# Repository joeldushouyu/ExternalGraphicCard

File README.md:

# ExternalGraphicCard

This Github repo contain the documentation for the USB-To-HDMI adapter(External Graphic Card) that I designed for my Senior Project.

The __USB To HDMI Adapter__(External Graphic Card) is an attempt to reproduce device that is similar to Startech's [USB32HD4k](https://www.startech.com/en-us/display-video-adapters/usb32hd4k) device that works on Linux, Ubuntu specifically. 

Currently, the device support video streaming up to 1080p at 30HZ. 

The device is compatible to most linux distribution that support by [evdi](https://github.com/DisplayLink/evdi). Currently, the device is tested and verified on Ubuntu 20.04.

When plugging the USb 3.0 Device into the host laptop and launch the C++ program, a new display monitor will be registered in OS and image data will stream out from the USb 3.0 port to the FPGA and output in HDMI signal.

**For more info**, please refer to the [user manual](Usermanual.md), [Technical Manual](TechnicalMaunaul.md), and the [Fabrication Plan Manual](./FabricationMaunal.md)

# Demonstration

## Video & Sound in Sync
[Video link](https://github.com/joeldushouyu/ExternalGraphicCard/blob/main/videoDirectory/video-sync.mp4)

## Drag window across monitors
[Video link](https://github.com/joeldushouyu/ExternalGraphicCard/blob/main/videoDirectory/drag-window-between-monitors.mp4)

## Browing  website
[Video link](https://github.com/joeldushouyu/ExternalGraphicCard/blob/main/videoDirectory/browsing-website.mp4)

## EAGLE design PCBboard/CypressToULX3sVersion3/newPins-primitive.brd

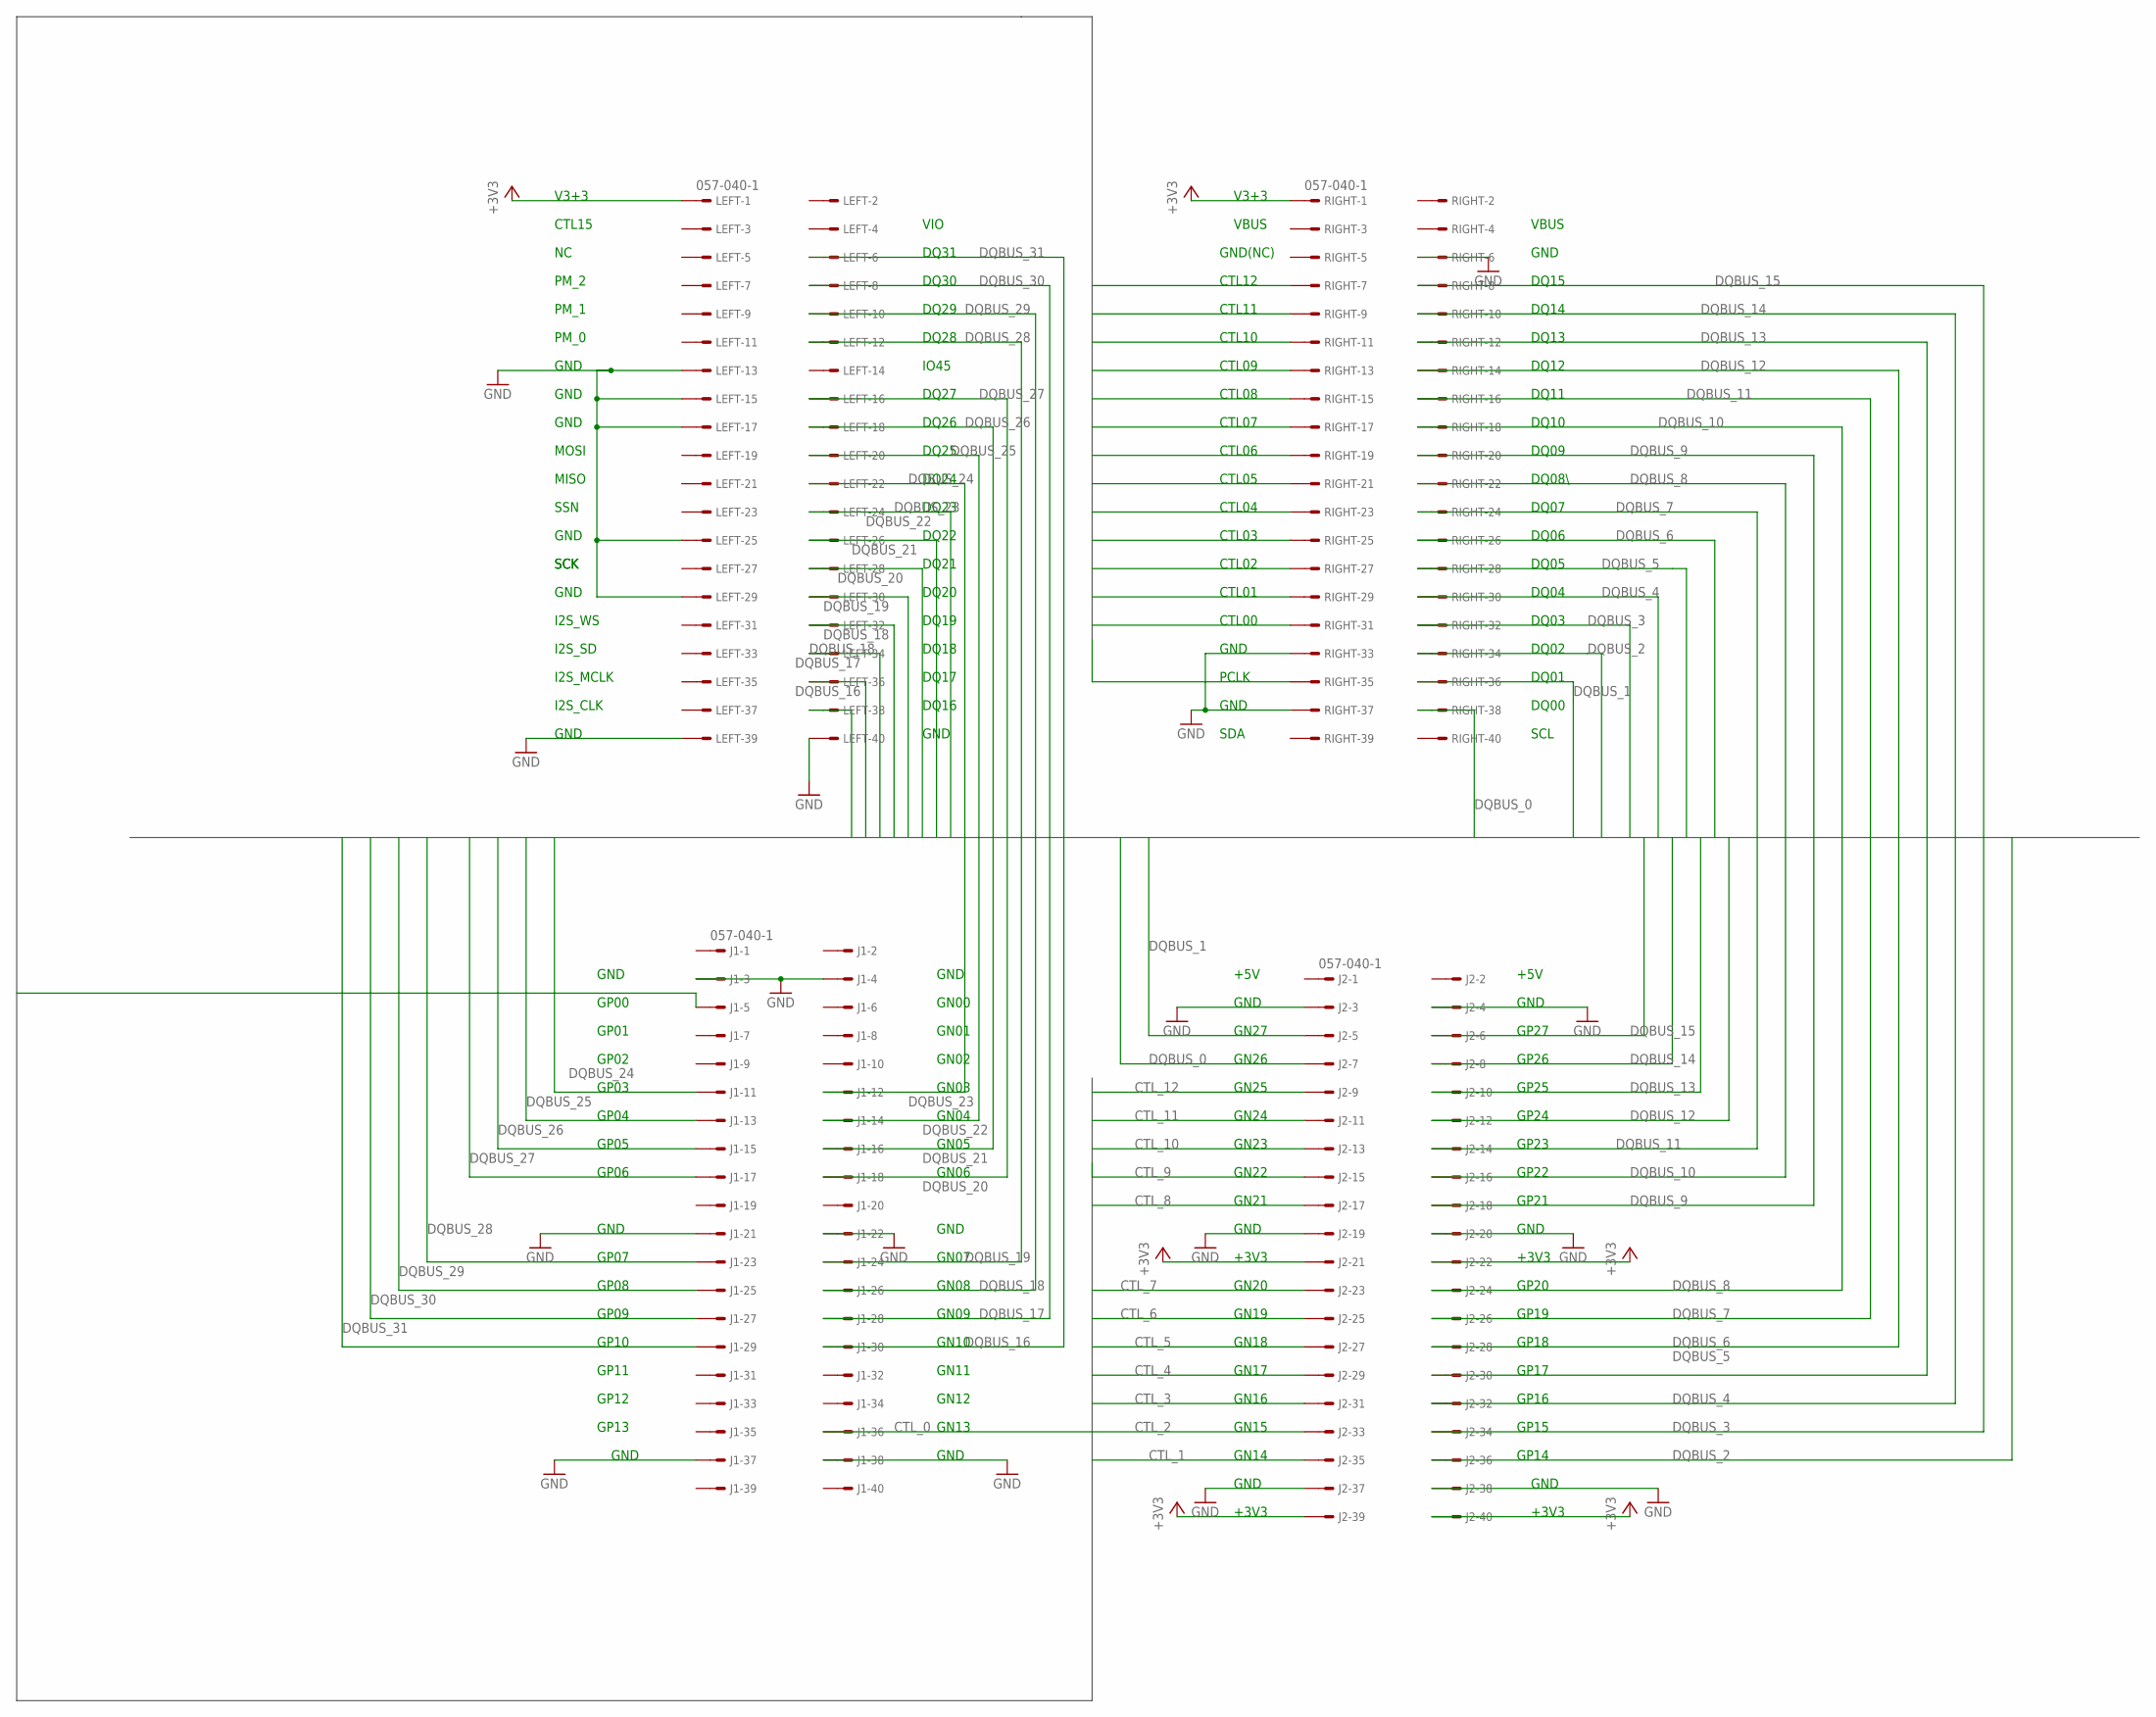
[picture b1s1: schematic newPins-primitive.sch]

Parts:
J1, J2: 057-040-1
LEFT: 057-040-1
RIGHT: 057-040-1

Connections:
+3V3: J2.21, J2.22, J2.39, J2.40, LEFT.1, RIGHT.1
CTL_0: J1.36, RIGHT.31
CTL_1: J2.35, RIGHT.29
CTL_2: J2.33, RIGHT.27
CTL_3: J2.31, RIGHT.25
CTL_4: J2.29, RIGHT.23
CTL_5: J2.27, RIGHT.21
CTL_6: J2.25, RIGHT.19
CTL_7: J2.23, RIGHT.17
CTL_8: J2.17, RIGHT.15
CTL_9: J2.15, RIGHT.13
CTL_10: J2.13, RIGHT.11
CTL_11: J2.11, RIGHT.9
CTL_12: J2.9, RIGHT.7
CTL_PCLK: J1.5, RIGHT.35
DQBUS_0: J2.7, RIGHT.38
DQBUS_1: J2.5, RIGHT.36
DQBUS_2: J2.36, RIGHT.34
DQBUS_3: J2.34, RIGHT.32
DQBUS_4: J2.32, RIGHT.30
DQBUS_5: J2.30, RIGHT.28
DQBUS_6: J2.28, RIGHT.26
DQBUS_7: J2.26, RIGHT.24
DQBUS_8: J2.24, RIGHT.22
DQBUS_9: J2.18, RIGHT.20
DQBUS_10: J2.16, RIGHT.18
DQBUS_11: J2.14, RIGHT.16
DQBUS_12: J2.12, RIGHT.14
DQBUS_13: J2.10, RIGHT.12
DQBUS_14: J2.8, RIGHT.10
DQBUS_15: J2.6, RIGHT.8
DQBUS_16: J1.30, LEFT.38
DQBUS_17: J1.28, LEFT.36
DQBUS_18: J1.26, LEFT.34
DQBUS_19: J1.24, LEFT.32
DQBUS_20: J1.18, LEFT.30
DQBUS_21: J1.16, LEFT.28
DQBUS_22: J1.14, LEFT.26
DQBUS_23: J1.12, LEFT.24
DQBUS_24: J1.11, LEFT.22
DQBUS_25: J1.13, LEFT.20
DQBUS_26: J1.15, LEFT.18
DQBUS_27: J1.17, LEFT.16
DQBUS_28: J1.23, LEFT.12
DQBUS_29: J1.25, LEFT.10
DQBUS_30: J1.27, LEFT.8
DQBUS_31: J1.29, LEFT.6
GND: J1.3, J1.4, J1.21, J1.22, J1.37, J1.38, J2.3, J2.4, J2.19, J2.20, J2.37, J2.38, LEFT.13, LEFT.15, LEFT.17, LEFT.25, LEFT.29, LEFT.39, LEFT.40, RIGHT.6, RIGHT.33, RIGHT.37

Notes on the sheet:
+5V
GND
+3V3
GP27
GP26
GP25
GP24
GP23
GP22
GP21
GP20
GP19
GP18
GP17
GP16
GP15
GP14
GN14
GN15
GN16
GN17
GN18
GN19
GN20
GN21
GN22
GN23
GN24
GN25
GN26
GN27
GN13
GN12
GN11
GN10
GN09
GN08
GN07
GN06
GN05

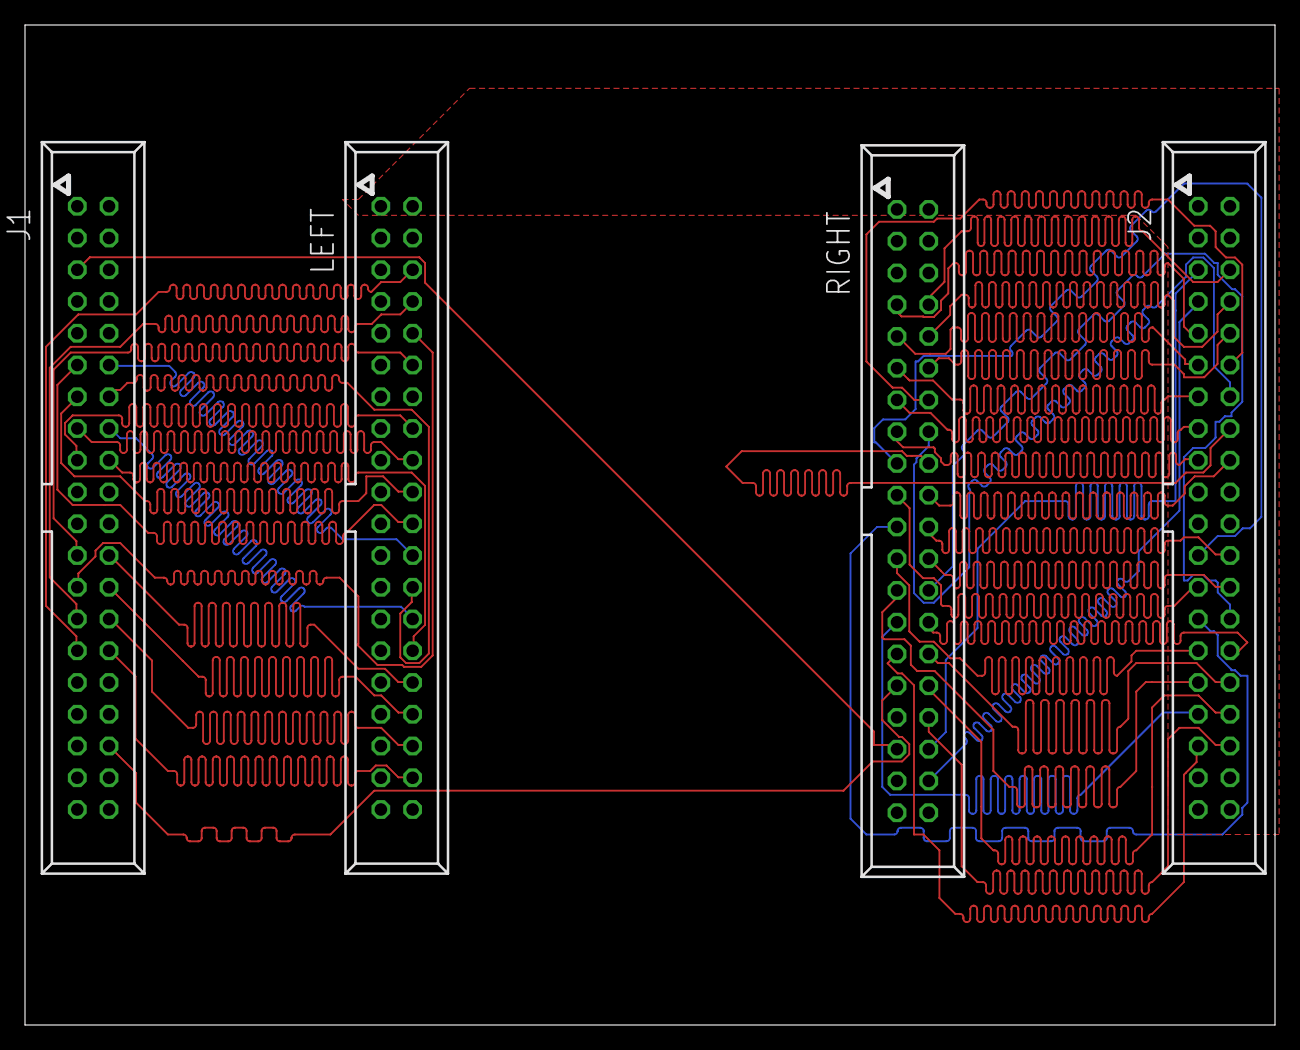
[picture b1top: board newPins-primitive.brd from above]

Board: 2 copper layers, 100.0 x 80.0 mm, 4 parts (0 on the bottom side), 48 nets.

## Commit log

2024-04-15 add .gif
2024-04-15 add gif on Readme.md
2024-04-15 update Readme.md to ensure correct link position
2024-04-15 modify readme to point to usermanual and technicalmanual
2024-04-27 Update Usermanual.md by fixing grammar issue
2024-04-27 fix: modify image
2024-04-27 update to documentation
2024-04-27 Update TechnicalMaunaul.md by updating grammar
2024-04-27 changes b adding a FabricationManual
2024-04-29 fix typo in usermanual
2024-04-29 fix error
